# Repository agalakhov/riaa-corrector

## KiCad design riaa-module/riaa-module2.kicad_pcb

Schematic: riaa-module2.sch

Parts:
C1, C2, C8, C9: 100p; C_0603_1608Metric
C3, C4, C5, C10, C11, C13: 100n; C_0603_1608Metric
C6, C7, C12, C14: C; C_0603_1608Metric
J1, J2: INPUT; PinHeader_1x03_P2.54mm_Horizontal
R1, R2, R9, R10: 22k5; R_0603_1608Metric
R3, R11: 50; R_0603_1608Metric
R4, R5, R6, R7, R8, R12, R13, R14, R15, R16: R; R_0603_1608Metric
U1, U3: AD8421; MSOP-8_3x3mm_P0.65mm
U2: OPA1604; TSSOP-14_4.4x5mm_P0.65mm

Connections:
+9V: C3.2, C10.2, U1.8 (Vs+), U2.4 (V+), U3.8 (Vs+)
-9V: C4.1, C11.1, U1.5 (Vs-), U2.11 (V-), U3.5 (Vs-)
/IN+L: C2.2, J1.1, R2.2, U1.4 (+)
/IN+R: C9.2, J2.1, R10.2, U3.4 (+)
/IN-L: C1.1, J1.3, R1.1, U1.1 (-)
/IN-R: C8.1, J2.3, R9.1, U3.1 (-)
/OUTPUT_L: C7.1, R6.1, R8.1, U2.8
/OUTPUT_R: C14.1, R15.1, R16.1, U2.7
/REFL: C5.1, C6.2, U1.6 (Ref), U2.14
/REFR: C12.2, C13.1, U2.1, U3.6 (Ref)
/SIGL: R4.2, U1.7
/SIGR: R12.2, U3.7
GND: R5.2, R13.2, U2.3 (+), U2.12 (+)
GNDPWR: C1.2, C2.1, C3.1, C4.2, C8.2, C9.1, C10.1, C11.2, J1.2, J2.2, R1.2, R2.1, R9.2, R10.1
unnamed: C5.2, R6.2, U2.13 (-)
unnamed: C6.1, R4.1, U2.10 (+)
unnamed: C7.2, R7.1, R8.2
unnamed: C12.1, R12.1, U2.5 (+)
unnamed: C13.2, R16.2, U2.2 (-)
unnamed: C14.2, R14.1, R15.2
unnamed: R3.1, U1.2 (Rg)
unnamed: R3.2, U1.3 (Rg)
unnamed: R5.1, R7.2, U2.9 (-)
unnamed: R11.1, U3.2 (Rg)
unnamed: R11.2, U3.3 (Rg)
unnamed: R13.1, R14.2, U2.6 (-)

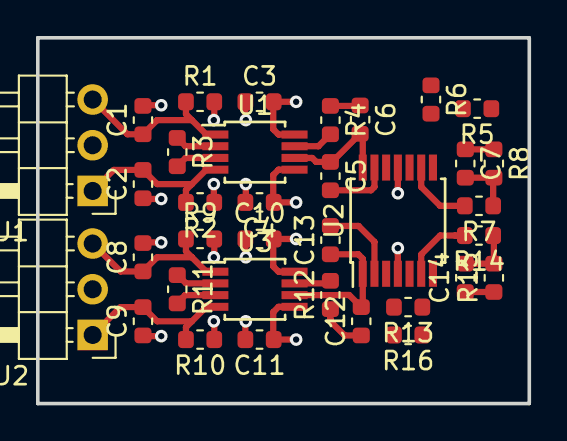
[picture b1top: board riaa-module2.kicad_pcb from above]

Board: 4 copper layers, 27.3 x 20.3 mm, 35 parts (0 on the bottom side), 26 nets.

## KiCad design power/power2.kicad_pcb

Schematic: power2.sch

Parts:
C1: C; C_Rect_L13.0mm_W5.0mm_P10.00mm_FKS3_FKP3_MKS4
C2, C3: 1000u; CP_Radial_D10.0mm_P5.00mm
C4, C5: 22u; CP_EIA-6032-15_Kemet-U_Pad2.25x2.35mm_HandSolder
C6: 10u; C_1206_3216Metric_Pad1.42x1.75mm_HandSolder
C7: 0.1u; C_0603_1608Metric_Pad1.05x0.95mm_HandSolder
C8, C10: 22u; C_0805_2012Metric_Pad1.15x1.40mm_HandSolder
C9: 75p; C_0603_1608Metric_Pad1.05x0.95mm_HandSolder
C11: 0.1u; C_1206_3216Metric_Pad1.42x1.75mm_HandSolder
D1: ABS2; Diode_Bridge_Diotec_SO-DIL-Slim
F1, F2: Fuse; Fuseholder_TR5_Littlefuse_No560_No460
J1: 230V; TerminalBlock_RND_205-00001_1x02_P5.00mm_Horizontal
J2: ANALOG; FanPinHeader_1x03_P2.54mm_Vertical
J3: DIGITAL; FanPinHeader_1x03_P2.54mm_Vertical
JP1: VCC_ON; PinHeader_1x02_P2.54mm_Vertical
L1: 15u; L_1210_3225Metric_Pad1.42x2.65mm_HandSolder
R1, R4: 40k2; R_0805_2012Metric_Pad1.15x1.40mm_HandSolder
R2, R3: 13k; R_0805_2012Metric_Pad1.15x1.40mm_HandSolder
R5: 49.9; R_0805_2012Metric_Pad1.15x1.40mm_HandSolder
R6: 13k3; R_0805_2012Metric_Pad1.15x1.40mm_HandSolder
R7: 470k; R_0805_2012Metric_Pad1.15x1.40mm_HandSolder
R8: 62k; R_0805_2012Metric_Pad1.15x1.40mm_HandSolder
R9: 100k; R_0805_2012Metric_Pad1.15x1.40mm_HandSolder
TR1: TRANSF3; Transformer_CHK_EI30-2VA_2xSec
U1: ADP7142AUZJ; TSOT-23-5
U2: ADP7182AUZJ; TSOT-23-5
U3: TPS54202; SOT-23-6

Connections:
/230VL: C1.1, F1.1, TR1.1
/230VN: C1.2, F2.1, TR1.2
/+5V: C8.1, C10.1, J3.1, L1.2, R5.1
/+12V: C4.1, J2.1, R1.1, U1.5
/-12V: C5.2, J2.3, R4.2, U2.5
/AC1: D1.4, TR1.3
/AC2: D1.3, TR1.6
/DC+: C2.1, C6.1, C11.1, D1.1, JP1.2, U1.1, U3.3 (VIN)
/DC-: C3.2, D1.2, U2.2
/EN12V: J3.3, U1.3, U2.3
/ENs: R7.2, R8.2, U3.5 (EN)
/FB+: R1.2, R2.1, U1.4
/FB-: R3.2, R4.1, U2.4
/FBs: C9.2, R6.1, R9.2, U3.4 (VFB)
/L: F1.2, J1.1
/N: F2.2, J1.2
GND: C2.2, C3.1, C4.2, C5.1, C6.2, C8.2, C10.2, C11.2, J2.2, J3.2, R2.2, R3.1, R6.2, R8.1, TR1.4, TR1.5, U1.2, U2.1, U3.1 (GND)
unnamed: C7.1, L1.1, U3.2 (SW)
unnamed: C7.2, U3.6 (VBST)
unnamed: C9.1, R5.2, R9.1
unnamed: JP1.1, R7.1

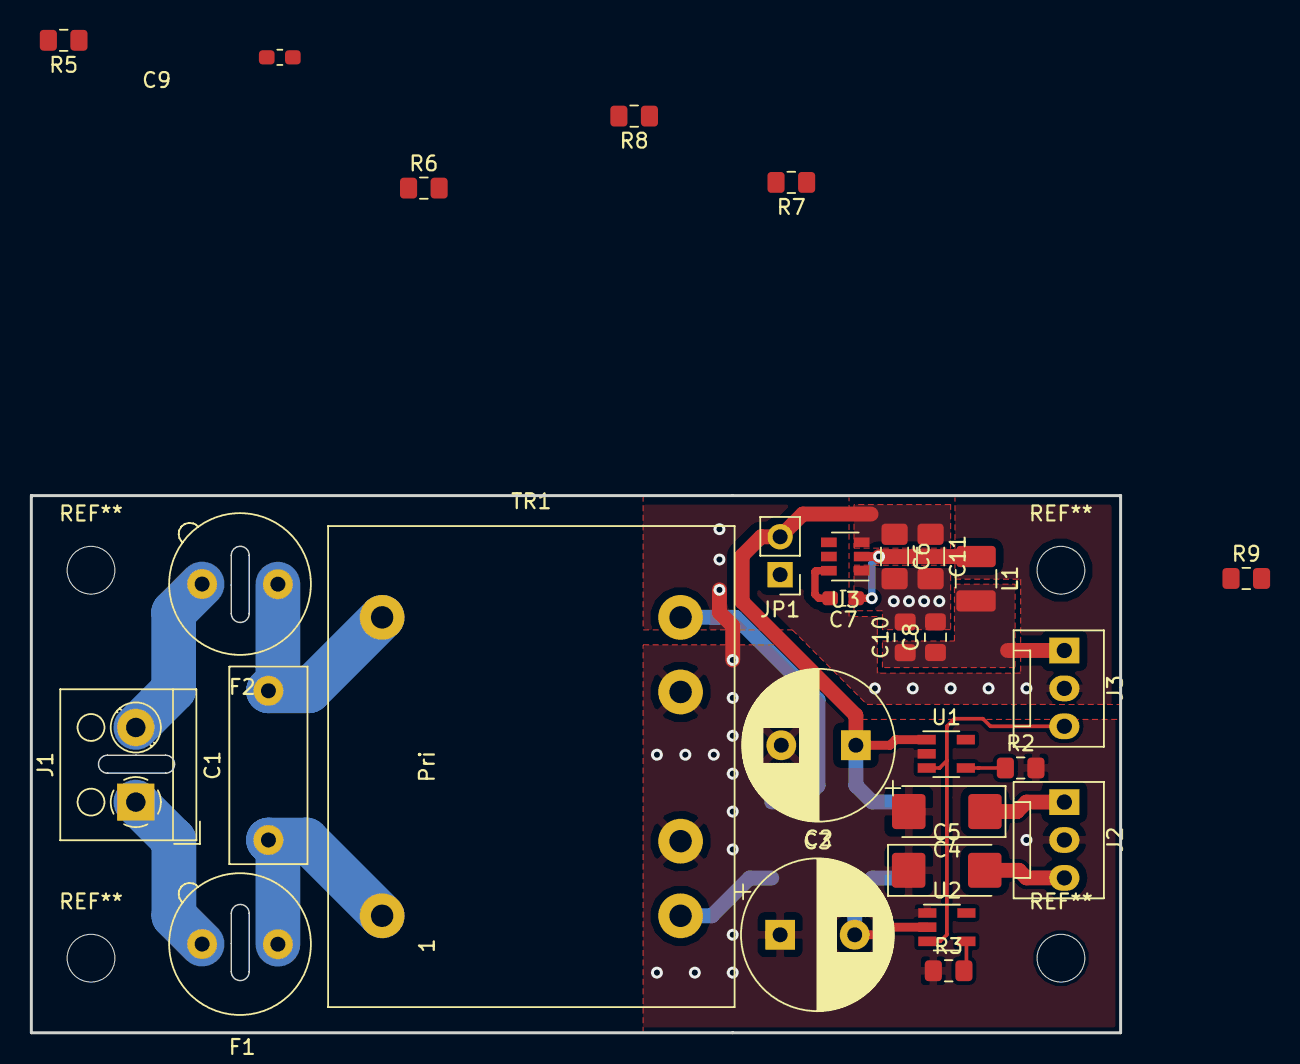
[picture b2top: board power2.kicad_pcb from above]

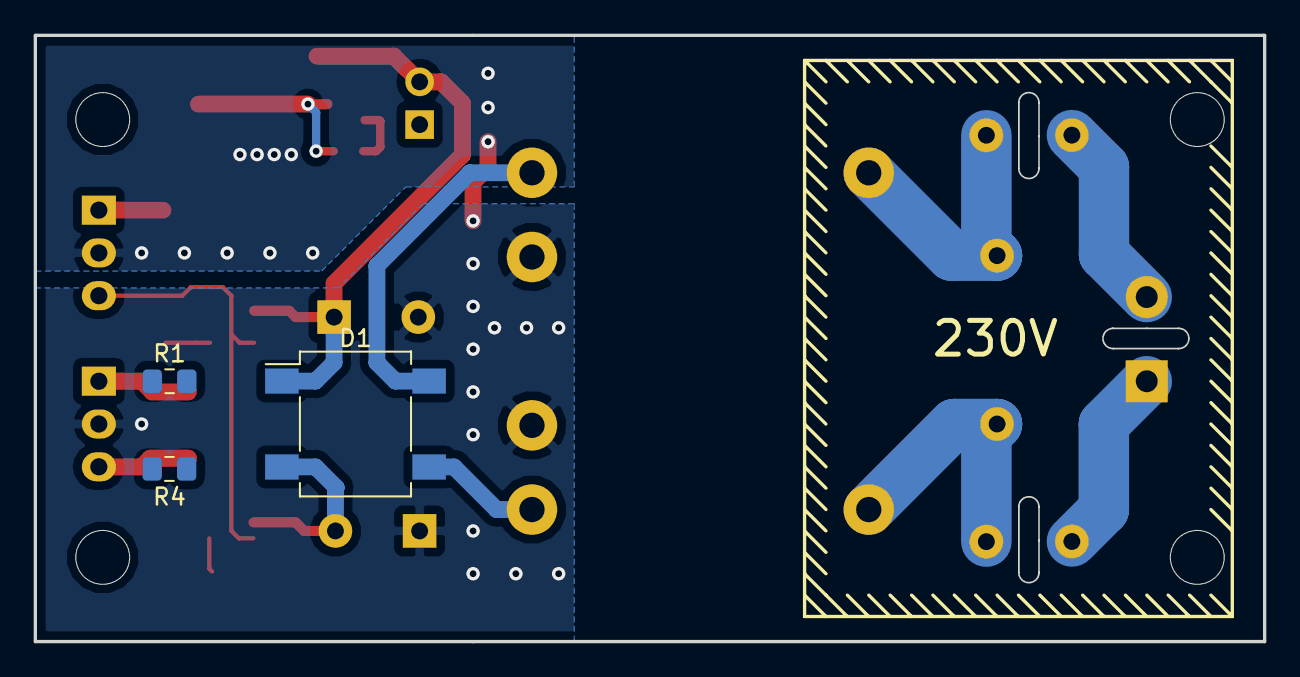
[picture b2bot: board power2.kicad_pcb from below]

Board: 2 copper layers, 73.0 x 36.0 mm, 32 parts (3 on the bottom side), 21 nets.

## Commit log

2019-07-20 Trafo library
2019-07-20 Power supply
2019-07-20 RIAA module
